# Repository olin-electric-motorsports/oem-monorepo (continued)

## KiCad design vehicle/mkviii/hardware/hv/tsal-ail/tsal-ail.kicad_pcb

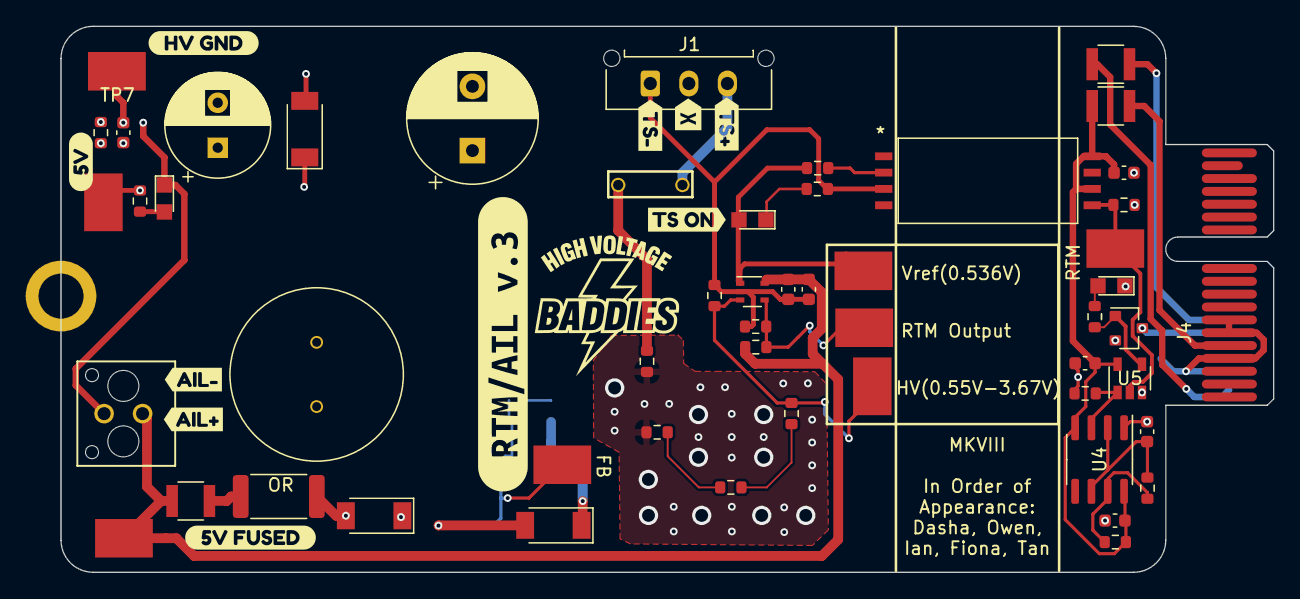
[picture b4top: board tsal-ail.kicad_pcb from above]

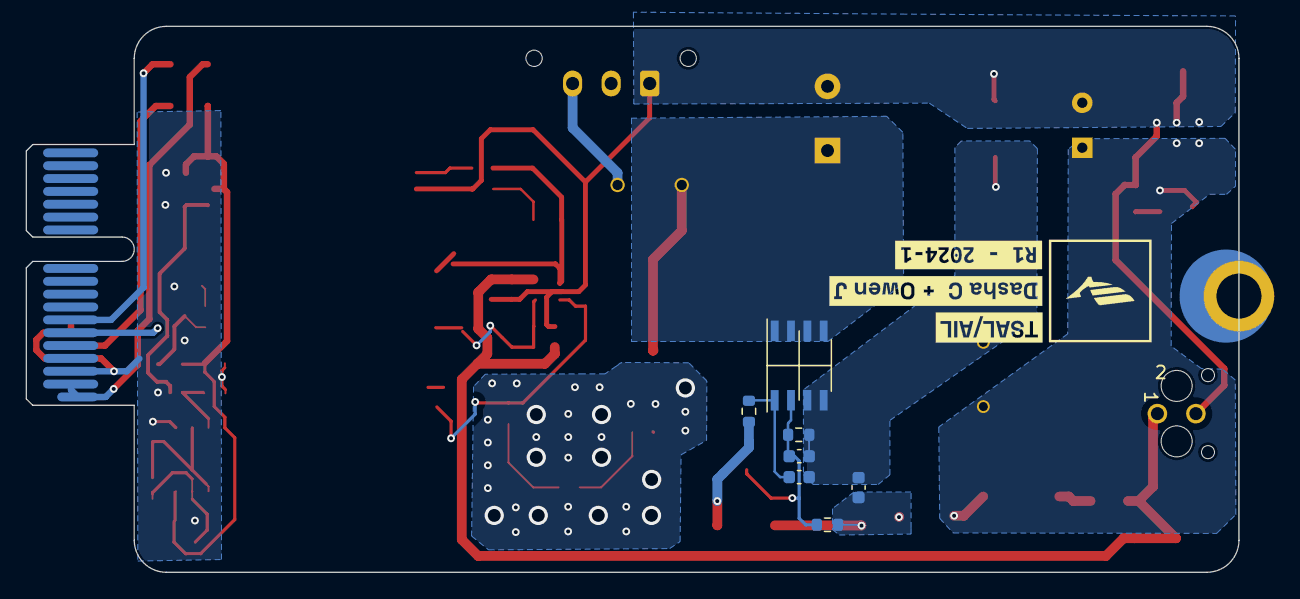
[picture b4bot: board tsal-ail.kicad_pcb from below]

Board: 2 copper layers, 94.4 x 42.5 mm, 74 parts (10 on the bottom side), 32 nets.

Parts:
C1: 10uF+; CP_Radial_D10.0mm_P5.00mm
C2: C_2.2uF; C_0603
C3: C_470pF; C_0603
C4: C_.22uF; C_0603
C5: C_10uF; C_0603
C6, C9, C10, C11, C12: 0.1uF; C_0603
C7: 100uF+; CP_Radial_D8.0mm_P3.50mm
C8: C_1uF; C_0603
D1, D2, D3: STTH1R06AF; D_SOD-128
D4: LED_0805; CHIPLED_0805
D5: LED_WHITE; CHIPLED_0805
D6: LED_AMBER; CHIPLED_0805
F1: F_21mA_420V
F2, F3: F_500mA_16V; Fuse_1210
F4: F_5000mA_16V; Fuse_1210
H1: M.2_MountingHole; M.2_Mount
J1: Conn_01x03; Molex_Micro-Fit_3.0_43650-0315_1x03_P3.00mm_Vertical
J2: MicroFit_V_2
J4: CONN_pcie_x1; pcie_x1
L1: L_1.2mH
Q2: SSM3K333R; SOT-23F
R1, R4, R7, R8: R_270K; R_0603
R2, R11, R12, R15: R_1K; R_0603
R3: R_120; R_0603
R5, R6, R17, R101: R_10K; R_0603
R9, R10: R_23.7K; R_0603
R13: R_3K; R_0603
R14: R_499; R_0603
R16: R_0_2512; R_2512_6332Metric
R20: R_6.04K; R_0603
R21: R_71.5K; R_0603
TP1: VREF; Test_Point_SMD
TP2: FB; Test_Point_SMD
TP3: 5V+_OUTPUT_FUSED; Test_Point_SMD
TP4: VIN; Test_Point_SMD
TP5: COMPARATOR_OUTPUT; Test_Point_SMD
TP6: 5V+_OUTPUT; Test_Point_SMD
TP7: TS-; Test_Point_SMD
TP8: TSAL_FLAG; Test_Point_SMD
U1: MP9488; Converter_DCDC_MPS_MP9488
U2: MCP6001; SOT-353_SC-70-5
U3: ACNT-H50L-500E
U4: NE555D; SOIC-8_3.9x4.9mm_P1.27mm
U5: U_GATE_SN74LVC1G08DBVR; SOT-23-5_OEM
kibuzzard-63AC91FD: G***; kibuzzard-63AC91FD
kibuzzard-63AC93EB: G***; kibuzzard-63AC93EB
kibuzzard-63AC93FC: G***; kibuzzard-63AC93FC
kibuzzard-63AC9220: G***; kibuzzard-63AC9220
kibuzzard-63AC9283: G***; kibuzzard-63AC9283
kibuzzard-63AC9446: G***; kibuzzard-63AC9446
kibuzzard-63AC9456: G***; kibuzzard-63AC9456
kibuzzard-63AD0077: G***; kibuzzard-63AD0077
kibuzzard-63D843BA: G***; kibuzzard-63D843BA
kibuzzard-63D84460: G***; kibuzzard-63D84460
kibuzzard-673C33E6: G***; kibuzzard-673C33E6
kibuzzard-6784A725: G***; kibuzzard-6784A725
kibuzzard-6784B342: G***; kibuzzard-6784B342

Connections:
+5V: C9.1, C10.1, C11.2, F3.1, R9.1, U3.6, U3.8, U4.4 (R), U4.8 (VCC), U5.5 (VCC)
+12V: F4.1, J4.A7 (io_2)
/+5V_TS_FUSED: C5.2, C6.2, F2.1, J2.1, R2.2, TP3.1, U2.5 (V+)
/FB: C3.1, R20.1, R21.2, TP2.1, U1.2 (FB)
/FLASH_2HZ: R101.1, U4.3 (Q), U5.1 (in)
/RTM_LIGHT-: J4.A6 (io_0), Q2.3 (D)
/SW: C2.2, C3.2, C4.2, D2.1 (K), L1.1, R20.2, U1.3 (SW), U1.4 (SW)
/TS+: F1.2, J1.3
/TS+_FUSED: C1.1, F1.1, R1.2, U1.5 (NC), U1.6 (NC), U1.7 (VIN), U1.8 (NC)
/TS-: C1.2, C5.1, C6.1, C7.2, C8.2, D2.2 (A), D5.1 (K), J1.1, J2.2, R3.2, R6.2, R12.2, R13.2, TP7.1, U2.2 (V-), U3.3
/TSAL_FLAG: R17.1, TP8.1, U3.5, U5.2 (in)
/VCC: C2.1, R5.2, U1.1 (VCC)
GND: C9.2, C10.2, C11.1, C12.1, D6.1 (K), J4.A3 (GND), J4.B4 (GND), J4.B6 (io_1), J4.B7 (io_3), Q2.2 (S), R17.2, R101.2, U4.1 (GND), U5.3 (GND)
unnamed: C4.1, D1.2 (A), D3.1 (K), R21.1
unnamed: D1.1 (K), R5.1
unnamed: C7.1, C8.1, D3.2 (A), L1.2, R13.1, R15.1, R16.2, TP6.1
unnamed: D4.2 (A), R14.2, TP5.1, U2.1
unnamed: D4.1 (K), R12.1
unnamed: D5.2 (A), R15.2
unnamed: D6.2 (A), R11.2
unnamed: F2.2, R16.1
unnamed: F4.2, J4.A1 (12V/3V(DA_ONLY)), J4.A2 (12V/3V(DA_ONLY))
unnamed: F3.2, J4.B5 (5V)
unnamed: Q2.1 (G), R11.1, U5.4 (out)
unnamed: R1.1, R4.2
unnamed: R4.1, R7.2
unnamed: R7.1, R8.2
unnamed: R14.1, U3.2
unnamed: R6.1, R8.1, TP4.1, U2.3 (+)
unnamed: R2.1, R3.1, TP1.1, U2.4 (-)
unnamed: R9.2, R10.1, U4.7 (DIS)
unnamed: C12.2, R10.2, U4.2 (TR), U4.6 (THR)

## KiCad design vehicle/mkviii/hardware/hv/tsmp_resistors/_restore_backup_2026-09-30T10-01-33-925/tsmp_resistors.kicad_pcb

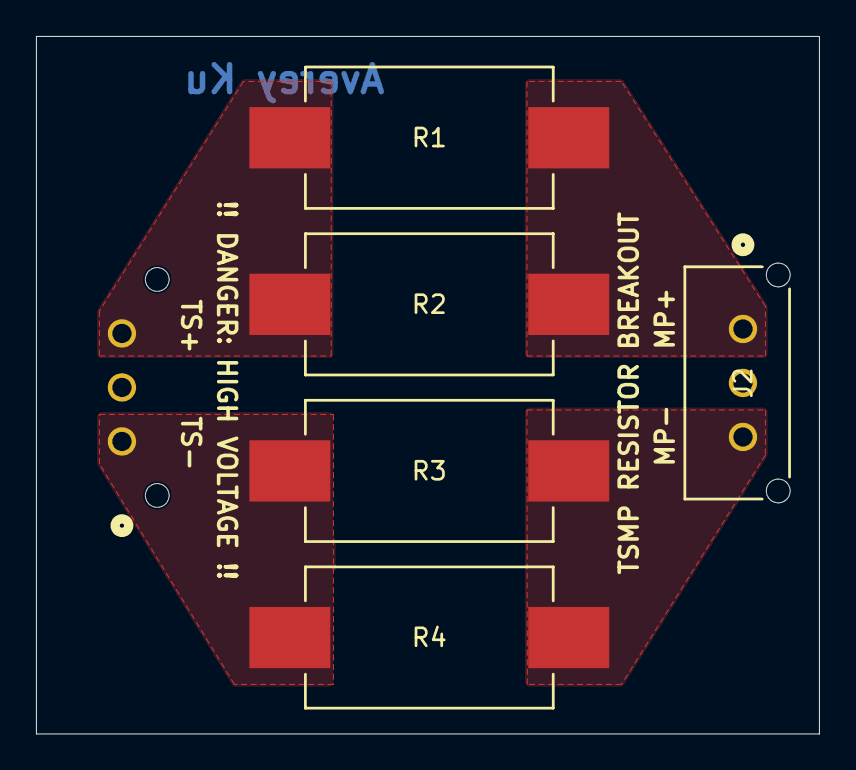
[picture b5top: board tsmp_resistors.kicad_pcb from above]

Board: 2 copper layers, 43.5 x 38.8 mm, 6 parts (1 on the bottom side), 4 nets, no tracks yet.

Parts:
J1: TS; J_Molex_Header_01x03_VT
J2: MP; J_Molex_Header_01x03_VT
R1, R2, R3, R4: R30K; R_5329_13573Metric

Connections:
/MP+: J2.1, R1.2, R2.2
/MP-: J2.3, R3.2, R4.2
/TS+: J1.3, R1.1, R2.1
/TS-: J1.1, R3.1, R4.1

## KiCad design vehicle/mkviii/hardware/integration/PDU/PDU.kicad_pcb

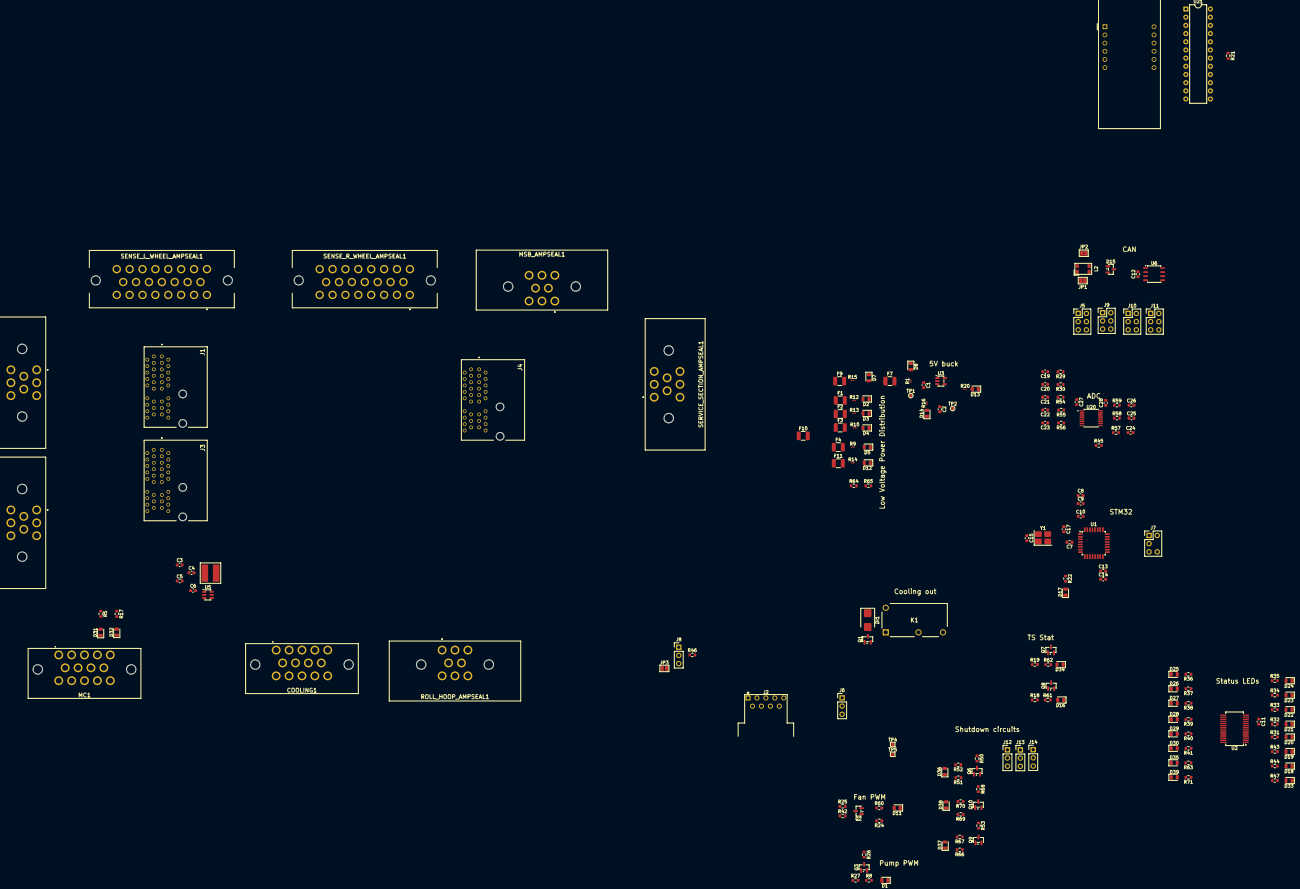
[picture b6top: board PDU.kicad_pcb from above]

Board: 2 copper layers, 182 parts (0 on the bottom side), 157 nets, no tracks yet.

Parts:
AUX_DEVICE_GPS1: J_Ampseal_08_RA; J_Ampseal_8_RA
C1, C4, C7, C8, C9, C11, C12: C_0.1uF; C_0603_1608Metric
C2, C14: C_1uF; C_0603_1608Metric
C3, C19, C20, C21, C22, C23, C24, C25, C26, C27, C28: C_10uF; C_0603_1608Metric
C5, C6: C_0.22uF; C_0603_1608Metric
C10: C_4.7uF; C_0603_1608Metric
C13: C_10nF; C_0603_1608Metric
C15, C17: C_30pF; C_0603_1608Metric
COOLING1: Ampseal_14_RA; J_Ampseal_14_RA
D1, D11, D16, D32, D34: LED_AMBER; LED_0805_2012Metric
D2, D3, D4, D5, D7, D8, D12: 12V; LED_0805_2012Metric
D13, D14, D17, D18, D19, D20, D21, D22, D23, D24, D25, D26, D27, D28, D29, D30, D33, D35, D39: 5V; LED_0805_2012Metric
D15: NUP2105L; SOT-23
D31: LED_RED; LED_0805_2012Metric
D36, D37, D38: LED_BLUE; LED_0805_2012Metric
DI1: SMBJ5355B-TP; D_SMB
F1: F_15A_12V; Fuse_1210_3225Metric
F2, F3, F4, F7, F9, F11: F_5A_12V; Fuse_1210_3225Metric
F10: F_20A_12V; Fuse_1210_3225Metric
J1, J3, J4: J_PCIe_x1
J2: CONN_DSub-9; DSUB-9_Pins_Horizontal_P2.77x2.54mm_EdgePinOffset9.40mm
J5, J9, J10, J11: CONN_02x03; PinHeader_2x03_P2.54mm_Vertical
J6, J8, J12, J13, J14: CONN_01X03; PinHeader_1x03_P2.54mm_Vertical
J7: J_Programming_Pin_Header; J_Programming_Pin_Header_Keyed
JP1, JP2: SolderJumper_2_Bridged; SolderJumper-2_P1.3mm_Bridged2Bar_Pad1.0x1.5mm
JP3: SolderJumper_2_Open; SolderJumper-2_P1.3mm_Open_Pad1.0x1.5mm
K1: G5Q-1A4-DC5; G5Q1A4DC5 (K_SPST-NO_10A_5V_TH - G5Q-1A4-DC5)
L1: L_3.9uH_2A; IND_BOURNS_SRR5018 (L_3.9uH_2A_55m_SMD)
L2: 1812CAN-104NRC; L_CommonModeChoke_Coilcraft_1812CAN
LV_MOBO_AMPSEAL1: Ampseal_08_RA; J_Ampseal_8_RA
MC1: Ampseal_14_RA; J_Ampseal_14_RA
MSB_AMPSEAL1: Ampseal_08_RA; J_Ampseal_8_RA
Q1, Q2, Q3, Q6, Q7, Q8, Q9, Q10: SSM3K333R; SOT-23
R1, R9, R10, R12, R13, R14, R15, R16, R20: R_200; R_0201_0603Metric
R5, R22, R31, R32, R33, R34, R35, R36, R37, R38, R39, R40, R41, R43, R44, R47, R63, R71: R_200; R_0603_1608Metric
R8, R17, R60, R61, R62: R_1k; R_0603_1608Metric
R18, R19, R24, R27, R50, R53, R68: R_10K; R_0603_1608Metric
R21: R_9.53k; R_0603_1608Metric
R25, R26, R29, R30, R42, R45, R54, R55, R56, R57, R58, R59: R_1K; R_0603_1608Metric
R46: R_120; R_0603_1608Metric
R51, R66, R69: R_100K; R_0603_1608Metric
R52, R67, R70: 3KR; R_0603_1608Metric
R64: R_20k; R_0603_1608Metric
R65: R_12k; R_0603_1608Metric
ROLL_HOOP_AMPSEAL1: Ampseal_08_RA; J_Ampseal_8_RA
SENSE_L_WHEEL_AMPSEAL1: Ampseal_23_RA; J_Ampseal_23_RA
SENSE_R_WHEEL_AMPSEAL1: Ampseal_23_RA; J_Ampseal_23_RA
SERVICE_SECTION_AMPSEAL1: Ampseal_08_RA; J_Ampseal_8_RA
TP1, TP2: TP_SMD; TestPoint_Pad_D1.0mm
TP4, TP5: TP_SMD; TestPoint_Pad_1.0x1.0mm
U1: STM32G441KBT6; LQFP-32_7x7mm_P0.8mm
U2: MCP23S17_SS; SSOP-28_5.3x10.2mm_P0.65mm
U3: TLV70450DBVR; SOT-23-5
U4: CC56-12SEKWA; CA56-12SEKWA
U5: AP63203WU-7; TSOT-23-6
U6: MCP2561-E_SN; JEITA_SOIC-8_3.9x4.9mm_P1.27mm
U20: ADC1283; TSSOP-16_4.4x5mm_P0.65mm
U21: MAX7221xNG; DIP-24_W7.62mm
Y1: X_Crystal_16MHz_18pF; Crystal_SMD_TXC_7M-4Pin_3.2x2.5mm_HandSoldering

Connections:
+3.3V: C5.1, C6.1, C8.1, C9.1, C10.1, C13.1, C14.1, J7.3, L1.2, U1.1 (VDD), U1.15 (VDDA), U1.17 (VDD), U5.1 (FB)
+5V: C11.2, C12.1, C27.1, C28.2, DI1.1 (K), J1.B5 (5V), J3.B5 (5V), J4.B5 (5V), K1.5, R5.1, R17.1, R18.1, R19.1, R21.1, R24.1, R27.1, R42.1, R45.1, R50.1, R53.1, R68.1, SENSE_L_WHEEL_AMPSEAL1.8, SENSE_R_WHEEL_AMPSEAL1.8, U2.9 (VDD), U6.3 (VDD), U21.19 (V+)
+12V: C3.1, F10.1, MSB_AMPSEAL1.4, MSB_AMPSEAL1.6, U5.2 (EN), U5.3 (VIN)
/12V_COOLING: F1.2, K1.3, R12.1
/12V_COOLING_OUT: COOLING1.3, COOLING1.4, K1.2, R25.1, R26.1
/12V_LV: F3.2, LV_MOBO_AMPSEAL1.4, LV_MOBO_AMPSEAL1.6, R10.1
/12V_MC: F4.2, MC1.7, R9.1
/12V_PDU: AUX_DEVICE_GPS1.4, ROLL_HOOP_AMPSEAL1.5, ROLL_HOOP_AMPSEAL1.7, SENSE_L_WHEEL_AMPSEAL1.12, SENSE_L_WHEEL_AMPSEAL1.16, SENSE_R_WHEEL_AMPSEAL1.12, SENSE_R_WHEEL_AMPSEAL1.16
/12V_SHDN: F11.2, J12.1, R14.1, R64.1, ROLL_HOOP_AMPSEAL1.1
/12V_SS: F2.2, R13.1, SERVICE_SECTION_AMPSEAL1.3
/CAN_1+: AUX_DEVICE_GPS1.2, J8.1, J9.1, JP3.2 (B), MSB_AMPSEAL1.2, TP4.1, U6.7 (CANH)
/CAN_1-: AUX_DEVICE_GPS1.3, J9.2, MSB_AMPSEAL1.3, R46.1, TP5.1, U6.6 (CANL)
/CAN_2+: AUX_DEVICE_GPS1.7, J1.A4 (CAN+), J3.A4 (CAN+), J4.A4 (CAN+), J9.3, J10.1, SENSE_R_WHEEL_AMPSEAL1.18
/CAN_2-: AUX_DEVICE_GPS1.6, J1.A5 (CAN-), J3.A5 (CAN-), J4.A5 (CAN-), J9.4, J10.2, SENSE_R_WHEEL_AMPSEAL1.19
/CAN_3+: J10.3, J11.1, SENSE_L_WHEEL_AMPSEAL1.18, SENSE_R_WHEEL_AMPSEAL1.20
/CAN_3-: J10.4, J11.2, SENSE_L_WHEEL_AMPSEAL1.19, SENSE_R_WHEEL_AMPSEAL1.21
/CAN_4+: J5.4, J11.3, MC1.8, SENSE_L_WHEEL_AMPSEAL1.20
/CAN_4-: J5.3, J11.4, MC1.9, SENSE_L_WHEEL_AMPSEAL1.21
/CAN_5+: D15.2 (K), J5.1, JP1.2 (B), L2.2, MC1.4
/CAN_5-: D15.1 (K), J5.2, JP2.1 (A), L2.3, MC1.5
/CAN_6+: JP2.2 (B), L2.4, LV_MOBO_AMPSEAL1.2
/CAN_6-: JP1.1 (A), L2.1, LV_MOBO_AMPSEAL1.3
/COOLING_EN: Q1.1 (G), U1.5 ((TIM2_ETR/TIM2_CH1/GPIO_EXTI0/ADC2_IN1/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)
/EXCITATION_L+: J4.B10 (io_9), SENSE_L_WHEEL_AMPSEAL1.3
/EXCITATION_L-: J4.A11 (io_10), SENSE_L_WHEEL_AMPSEAL1.4
/EXCITATION_R+: J4.B7 (io_3), SENSE_R_WHEEL_AMPSEAL1.3
/EXCITATION_R-: J4.A8 (io_4), SENSE_R_WHEEL_AMPSEAL1.4
/E_STOP_COM: J12.2, J13.1, Q10.1 (G), R69.1, R70.1, ROLL_HOOP_AMPSEAL1.2
/E_STOP_R_OUT: J13.2, J14.1, MC1.11, Q6.1 (G), R51.1, R52.1, ROLL_HOOP_AMPSEAL1.3
/FAN_PWM: Q2.1 (G), R24.2, R60.1, U1.7 ((TIM15_CH1/USART2_TX/TIM2_CH3/GPIO_EXTI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)
/HVIL_OUT: J14.2, LV_MOBO_AMPSEAL1.8, MC1.10, Q9.1 (G), R66.1, R67.1
/INVERTER_FAULT: D31.1 (K), MC1.13
/INVERTER_GND: J2.5, J6.2, MC1.6
/INVERTER_PROGRAM: J6.3, MC1.12
/INVERTER_RXD: J2.2, MC1.1
/INVERTER_START_OK: D32.1 (K), MC1.14
/INVERTER_TXD: J2.3, MC1.2
/LVDB_Power/5V: C2.1, R16.1, R20.1, TP2.1, U3.3 (OUT)
/LVDB_Power/5V_Buck/BUCK_VIN: F7.1, F9.2, R15.1
/Microcontroller/CAN_RX: U1.22 ((FDCAN1_TX/GPIO_EXTI12)PA12), U6.4 (RXD)
/Microcontroller/CAN_TX: U1.21 ((FDCAN1_RX/GPIO_EXTI11)PA11), U6.1 (TXD)
/Microcontroller/CS_ADC: U1.29 ((TIM4_CH1/TIM16_CH1N/GPIO_EXTI6)PB6), U20.1 (~CS)
/Microcontroller/CS_DISP: U1.28 ((TIM17_CH1/SPI1_MOSI/TIM3_CH2/TIM16_BKI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), U21.12 (~CS)
/Microcontroller/CS_IO: U1.30 ((TIM3_CH4/TIM4_CH2/TIM17_CH1N/GPIO_EXTI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), U2.11 (~CS)
/Microcontroller/DIG_0: U4.12 (CC1), U21.2 (DIG_0)
/Microcontroller/DIG_1: U4.9 (CC2), U21.11 (DIG_1)
/Microcontroller/DIG_2: U4.8 (CC3), U21.6 (DIG_2)
/Microcontroller/DIG_3: U4.6 (CC4), U21.7 (DIG_3)
/Microcontroller/HB_LED: R22.1, U1.9 ((USART2_CK/TIM3_CH2/GPIO_EXTI4/ADC2_IN1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)
/Microcontroller/MISO: U1.11 ((TIM3_CH1/TIM16_CH1/GPIO_EXTI6/ADC2_IN3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), U2.14 (SO), U20.15 (DOUT)
/Microcontroller/MOSI: U1.12 ((TIM3_CH2/TIM17_CH1/GPIO_EXTI7/ADC2_IN4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), U2.13 (SI), U20.14 (DIN), U21.1 (DIN)
/Microcontroller/RESET_IO: U1.31 ((TIM4_CH3/TIM16_CH1/GPIO_EXTI8)PB8-BOOT0), U2.18 (~RESET)
/Microcontroller/SCK: U1.10 ((TIM2_ETR/TIM2_CH1/GPIO_EXTI5/ADC2_IN13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), U2.12 (SCK), U20.16 (SCLK), U21.13 (CLK)
/Microcontroller/SWCLK: J7.5, U1.24 ((SYS_JTCK-SWCLK/GPIO_EXTI14)PA14)
/Microcontroller/SWDIO: J7.1, U1.23 ((SYS_JTMS-SWDIO/GPIO_EXTI13)PA13)
/Microcontroller/nRST: C7.1, J7.4, U1.4 ((GPIO_EXTI10)PG10-NRST)
/PUMP_PWM: Q3.1 (G), R8.1, R27.2, U1.8 ((TIM15_CH2/USART2_RX/TIM2_CH4/GPIO_EXTI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)
/SIGNAL_L+: J4.B12 (io_13), SENSE_L_WHEEL_AMPSEAL1.6
/SIGNAL_L-: J4.B11 (io_11), SENSE_L_WHEEL_AMPSEAL1.5
/SIGNAL_R+: J4.B9 (io_7), SENSE_R_WHEEL_AMPSEAL1.6
/SIGNAL_R-: J4.B8 (io_5), SENSE_R_WHEEL_AMPSEAL1.5
/SIG_FAN: COOLING1.9, Q2.3 (D), R25.2, R42.2
/SIG_PUMP: COOLING1.7, Q3.3 (D), R26.2
/SIG_TEMP: COOLING1.6, R45.2, R57.1
/SS_ESTOP_L: Q10.3 (D), R68.2, U1.20 ((TIM2_CH4/USART1_RX/TIM17_BKIN/GPIO_EXT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)
/SS_ESTOP_R: Q6.3 (D), R50.2, U1.25 ((TIM2_ETR/TIM2_CH1/GPIO_EXTI15)PA15)
/SS_GLVMS: R64.2, R65.1, U1.26 ((TIM3_ETR/SPI1_SCK/TIM4_ETR/TIM2_CH2/GP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)
/SS_MC: Q9.3 (D), R53.2, U1.6 ((TIM15_CH1N/TIM2_CH2/GPIO_EXTI1/ADC2_IN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)
/SUS_TRAVEL_L_SIG: J3.B6 (io_1), SENSE_L_WHEEL_AMPSEAL1.10
/SUS_TRAVEL_R_SIG: J3.A7 (io_2), SENSE_R_WHEEL_AMPSEAL1.10
/TSMS_IN: MSB_AMPSEAL1.7, SERVICE_SECTION_AMPSEAL1.7
/TSMS_OUT: MSB_AMPSEAL1.8, SERVICE_SECTION_AMPSEAL1.8
/TS_STAT_G: Q8.1 (G), R18.2, R61.1, U1.18 ((TIM4_ETR/USART1_CK/GPIO_EXTI8)PA8)
/TS_STAT_G_12V: Q8.3 (D), ROLL_HOOP_AMPSEAL1.6
/TS_STAT_R: Q7.1 (G), R19.2, R62.1, U1.19 ((TIM2_CH3/TIM15_BKIN/USART1_TX/GPIO_EXT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)
/TS_STAT_R_12V: Q7.3 (D), ROLL_HOOP_AMPSEAL1.8
/WHEEL_SPEED_L_SIG: J1.B8 (io_5), SENSE_L_WHEEL_AMPSEAL1.14
/WHEEL_SPEED_R_SIG: J1.B6 (io_1), SENSE_R_WHEEL_AMPSEAL1.14
GND: AUX_DEVICE_GPS1.1, AUX_DEVICE_GPS1.5, C1.2, C2.2, C3.2, C5.2, C6.2, C7.2, C8.2, C9.2, C10.2, C11.1, C12.2, C13.2, C14.2, C15.1, C17.1, C19.2, C20.2, C21.2, C22.2, C23.2, C24.2, C25.2, C26.2, COOLING1.2, COOLING1.5, COOLING1.8, D1.1 (K), D2.1 (K), D3.1 (K), D4.1 (K), D5.1 (K), D7.1 (K), D8.1 (K), D11.1 (K), D12.1 (K), D13.1 (K), D14.1 (K), D15.3 (A), D16.1 (K), D17.1 (K), D18.1 (K), D19.1 (K), D20.1 (K), D21.1 (K), D22.1 (K), D23.1 (K), D24.1 (K), D25.1 (K), D26.1 (K), D27.1 (K), D28.1 (K), D29.1 (K), D30.1 (K), D33.1 (K), D34.1 (K), D35.1 (K), D36.1 (K), D37.1 (K), D38.1 (K), D39.1 (K), J1.A3 (GND), J1.B4 (GND), J3.A3 (GND), J3.B4 (GND), J4.A1 (12V/3V(DA_ONLY)), J4.A3 (GND), J4.A6 (io_0), J4.A9 (io_6), J4.A10 (io_8), J4.A12 (io_12), J4.A13 (io_14), J4.B4 (GND), J7.2, LV_MOBO_AMPSEAL1.1, LV_MOBO_AMPSEAL1.5, MC1.3, MSB_AMPSEAL1.1, MSB_AMPSEAL1.5, Q1.2 (S), Q2.2 (S), Q3.2 (S), Q6.2 (S), Q7.2 (S), Q8.2 (S), Q9.2 (S), Q10.2 (S), R51.2, R65.2, R66.2, R69.2, SENSE_L_WHEEL_AMPSEAL1.9, SENSE_L_WHEEL_AMPSEAL1.13, SENSE_L_WHEEL_AMPSEAL1.17, SENSE_L_WHEEL_AMPSEAL1.22, SENSE_L_WHEEL_AMPSEAL1.23, SENSE_R_WHEEL_AMPSEAL1.9, SENSE_R_WHEEL_AMPSEAL1.13, SENSE_R_WHEEL_AMPSEAL1.17, SENSE_R_WHEEL_AMPSEAL1.22, SENSE_R_WHEEL_AMPSEAL1.23, SERVICE_SECTION_AMPSEAL1.1, SERVICE_SECTION_AMPSEAL1.2, U1.14 (VSSA), U1.16 (VSS), U1.32 (VSS), U2.10 (VSS), U3.1 (GND), U3.4 (NC_1), U3.5 (NC_2), U5.4 (GND), U6.2 (VSS), U6.8 (STBY), U20.3 (AGND), U20.12 (DGND), U21.4 (GND), U21.9 (GND), Y1.2, Y1.4
unnamed: D1.2 (A), R8.2
unnamed: D2.2 (A), R12.2
unnamed: D3.2 (A), R13.2
unnamed: D4.2 (A), R10.2
unnamed: D5.2 (A), R9.2
unnamed: D7.2 (A), R15.2
unnamed: D8.2 (A), R1.2
unnamed: D11.2 (A), R60.2
unnamed: D12.2 (A), R14.2
unnamed: D13.2 (A), R20.2
unnamed: D14.2 (A), R16.2
unnamed: D16.2 (A), R61.2
unnamed: D17.2 (A), R22.2
unnamed: D18.2 (A), R44.2
unnamed: D19.2 (A), R43.2
unnamed: D20.2 (A), R31.2
unnamed: D21.2 (A), R32.2
unnamed: D22.2 (A), R33.2
unnamed: D23.2 (A), R34.2
unnamed: D24.2 (A), R35.2
unnamed: D25.2 (A), R36.2
unnamed: D26.2 (A), R37.2
unnamed: D27.2 (A), R38.2
unnamed: D28.2 (A), R39.2
unnamed: D29.2 (A), R40.2
unnamed: D30.2 (A), R41.2
unnamed: D31.2 (A), R5.2
unnamed: D32.2 (A), R17.2
unnamed: D33.2 (A), R47.2
unnamed: D34.2 (A), R62.2
unnamed: D35.2 (A), R63.2
unnamed: D36.2 (A), R52.2
unnamed: D37.2 (A), R67.2
unnamed: D38.2 (A), R70.2
unnamed: D39.2 (A), R71.2
unnamed: DI1.2 (A), K1.1, Q1.3 (D)
unnamed: F1.1, F2.1, F3.1, F4.1, F9.1, F10.2, F11.1
unnamed: J8.2, JP3.1 (A), R46.2
unnamed: C17.2, U1.2 (PF0-OSC_IN), Y1.3
unnamed: C15.2, U1.3 (PF1-OSC_OUT), Y1.1
unnamed: R36.1, U2.21 (GPA0)
unnamed: R37.1, U2.22 (GPA1)
unnamed: R38.1, U2.23 (GPA2)
unnamed: R39.1, U2.24 (GPA3)
unnamed: R40.1, U2.25 (GPA4)
unnamed: R41.1, U2.26 (GPA5)
unnamed: R63.1, U2.27 (GPA6)
unnamed: R71.1, U2.28 (GPA7)
unnamed: R47.1, U2.1 (GPB0)
unnamed: R44.1, U2.2 (GPB1)
unnamed: R43.1, U2.3 (GPB2)
unnamed: R31.1, U2.4 (GPB3)
unnamed: R32.1, U2.5 (GPB4)
unnamed: R33.1, U2.6 (GPB5)
unnamed: R34.1, U2.7 (GPB6)
unnamed: R35.1, U2.8 (GPB7)
unnamed: C1.1, F7.2, R1.1, TP1.1, U3.2 (IN)
unnamed: C4.1, U5.6 (BST)
unnamed: C4.2, L1.1, U5.5 (SW)
unnamed: C27.2, U20.2 (AVCC)
unnamed: C28.1, U20.13 (DVCC)
unnamed: C19.1, R29.2, U20.4 (IN0)
unnamed: C20.1, R30.2, U20.5 (IN1)
unnamed: C21.1, R54.2, U20.6 (IN2)
unnamed: C22.1, R55.2, U20.7 (IN3)
unnamed: C23.1, R56.2, U20.8 (IN4)
unnamed: C24.1, R57.2, U20.9 (IN5)
unnamed: C25.1, R58.2, U20.10 (IN6)
unnamed: C26.1, R59.2, U20.11 (IN7)
unnamed: R21.2, U21.18 (ISET)
unnamed: U4.11 (a), U21.14 (SEG_A)
unnamed: U4.7 (b), U21.16 (SEG_B)
unnamed: U4.4 (c), U21.20 (SEG_C)
unnamed: U4.2 (d), U21.23 (SEG_D)
unnamed: U4.3 (DPX), U21.22 (SEG_DP)
unnamed: U4.1 (e), U21.21 (SEG_E)
unnamed: U4.10 (f), U21.15 (SEG_F)
unnamed: U4.5 (g), U21.17 (SEG_G)
